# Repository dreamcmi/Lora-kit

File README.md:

# Lora-Kit

#### 介绍
基于M-HL10串口lora模组做的一个测试板

kicad格式文件，gerber，bom都有

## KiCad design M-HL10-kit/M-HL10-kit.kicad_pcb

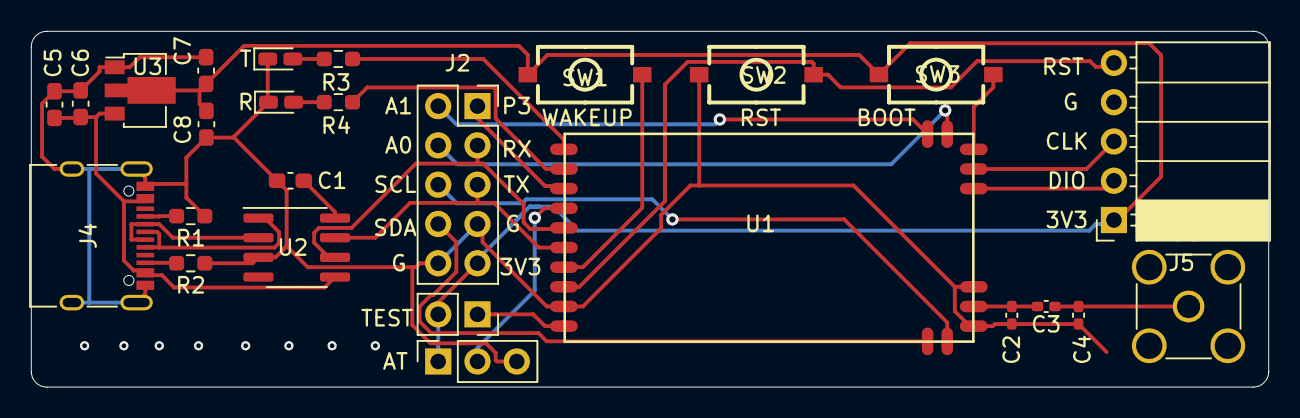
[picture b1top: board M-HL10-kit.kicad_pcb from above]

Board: 2 copper layers, 80.0 x 23.0 mm, 26 parts (0 on the bottom side), 28 nets.

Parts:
AT: Conn_01x03_Female; PinSocket_1x03_P2.54mm_Vertical
C1, C5, C6, C7, C8: 0.1uf; C_0603_1608Metric_Pad1.08x0.95mm_HandSolder
C2, C4: NF; C_0402_1005Metric_Pad0.74x0.62mm_HandSolder
C3: 100pf; C_0402_1005Metric_Pad0.74x0.62mm_HandSolder
J2: Conn_02x05_Odd_Even; PinSocket_2x05_P2.54mm_Vertical
J4: USB_C_Receptacle_USB2.0; USB_C_Receptacle_XKB_U262-16XN-4BVC11
J5: Conn_01x05_Female; PinSocket_1x05_P2.54mm_Horizontal
J6: Conn_01x02_Female; SMA_Amphenol_901-144_Vertical
R: R_LED; LED_0603_1608Metric_Castellated
R1, R2: 5.1K; R_0603_1608Metric_Pad0.98x0.95mm_HandSolder
R3, R4: 1K; R_0603_1608Metric_Pad0.98x0.95mm_HandSolder
SW1, SW2, SW3: TS-1101-B-W; KEY-SMD_2P-L6.0-W3.6-P7.4-LS8.0-L
T: T_LED; LED_0603_1608Metric_Castellated
TEST: Conn_01x02_Female; PinSocket_1x02_P2.54mm_Vertical
U1: M-HL10
U2: CH330N; SOIC-8_3.9x4.9mm_P1.27mm
U3: AMS1117-3.3; SOT-89-3

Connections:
+3V3: AT.1, C7.1, C8.1, J2.9, J5.1, SW1.1, SW3.1, TEST.2, U3.2
+5V: C5.1, C6.1, J4.A4, J4.A9, J4.B4, J4.B9, U2.5, U3.3
/A0: J2.4, U1.19
/A1: J2.2, U1.20
/AT: AT.2, U1.4
/BOOT: SW3.2, U1.18
/D+: J4.A6, J4.B6, U2.1
/D-: J4.A7, J4.B7, U2.2
/P1: R3.1, U1.1
/P2: R4.1, U1.2
/P3: J2.1, U1.3
/RST: J5.5, SW2.2, U1.8
/RX: J2.3, U1.5, U2.6
/SCL: J2.6, U1.12
/SDA: J2.8, U1.11
/TX: J2.5, U1.6, U2.7
/WKUP: SW1.2, U1.7
GND: AT.3, C1.2, C2.1, C4.1, C5.2, C6.2, C7.2, C8.2, J2.7, J2.10, J4.A1, J4.A12, J4.B1, J4.B12, J4.S1, J5.4, J6.2, R.1, R1.1, R2.1, SW2.1, T.1, U1.9, U1.13, U1.15, U2.3, U3.1
unnamed: C1.1, U2.8
unnamed: C2.2, C3.2, U1.14
unnamed: C3.1, C4.2, J6.1
unnamed: R3.2, T.2
unnamed: R.2, R4.2
unnamed: TEST.1, U1.10
unnamed: J4.A5, R1.2
unnamed: J4.B5, R2.2
unnamed: J5.2, U1.16
unnamed: J5.3, U1.17

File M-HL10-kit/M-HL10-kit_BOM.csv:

"Comment","Description","Designator","Footprint","LibRef","Pins","Quantity","PartNumber","url",
"100pf","desc","C3,","C_0402_1005Metric_Pad0.74x0.62mm_HandSolder","libref","2","1","","",
"NF","desc","C4,C2,","C_0402_1005Metric_Pad0.74x0.62mm_HandSolder","libref","2","2","","",
"0.1uf","desc","C8,C6,C1,C7,C5,","C_0603_1608Metric_Pad1.08x0.95mm_HandSolder","libref","2","5","","",
"R_LED","desc","R,","LED_0603_1608Metric_Castellated","libref","2","1","","",
"5.1K","desc","R2,R1,","R_0603_1608Metric_Pad0.98x0.95mm_HandSolder","libref","2","2","","",
"1K","desc","R4,R3,","R_0603_1608Metric_Pad0.98x0.95mm_HandSolder","libref","2","2","","",
"TS-1101-B-W","desc","SW3,SW2,SW1,","KEY-SMD_2P-L6.0-W3.6-P7.4-LS8.0-L","libref","2","3","","",
"T_LED","desc","T,","LED_0603_1608Metric_Castellated","libref","2","1","","",
"M-HL10","desc","U1,","M-HL10","libref","20","1","","",
"CH330N","desc","U2,","SOIC-8_3.9x4.9mm_P1.27mm","libref","8","1","","",
"AMS1117-3.3","desc","U3,","SOT-89-3","libref","3","1","","",
"Through Hole Items ",
"Conn_01x03_Female","desc","AT,","PinSocket_1x03_P2.54mm_Vertical","libref","3","1","","",
"Conn_02x05_Odd_Even","desc","J2,","PinSocket_2x05_P2.54mm_Vertical","libref","10","1","","",
"USB_C_Receptacle_USB2.0","desc","J4,","USB_C_Receptacle_XKB_U262-16XN-4BVC11","libref","22","1","","",
"Conn_01x05_Female","desc","J5,","PinSocket_1x05_P2.54mm_Horizontal","libref","5","1","","",
"Conn_01x02_Female","desc","J6,","SMA_Amphenol_901-144_Vertical","libref","5","1","","",
"Conn_01x02_Female","desc","TEST,","PinSocket_1x02_P2.54mm_Vertical","libref","2","1","","",

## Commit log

2021-02-24 add MIT LICENSE
2021-02-24 add project
2021-02-26 add english md
2021-02-26 删除多余的文件
